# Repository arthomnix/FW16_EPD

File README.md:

# Framework Laptop 16 Touchscreen E-Paper Input Module

Touchscreen E-paper medium size input module for the Framework Laptop 16

_As featured on the [Framework 16 product page](https://frame.work/laptop16) and [Framework 2nd Gen Event](https://www.youtube.com/watch?v=-8k7jTF_JCg)_

**Firmware and software:** https://github.com/arthomnix/epd_firmware (also mirrored on [Tangled](https://tangled.sh/@arthomnix.dev/eepy))

## Legal

Copyright © 2024 arthomnix

This work is licensed under [Creative Commons Attribution-ShareAlike 4.0 International](https://creativecommons.org/licenses/by-sa/4.0).

Framework Laptop 16 Input Module footprints (`InputModule.pretty` folder) © 2023 Framework Computer, Inc. Licensed under [Creative Commons Attribution 4.0 International](https://creativecommons.org/licenses/by/4.0). Original available at https://github.com/FrameworkComputer/InputModules.

Hirose FH34SRJ footprints and symbols (`Hirose_FPC.pretty` folder; `FH34SRJ_*.kicad_sym`) © 2013-2024 SnapMagic. Licensed under [Creative Commons Attribution-ShareAlike 4.0 International](https://creativecommons.org/licenses/by-sa/4.0) with [Design Exception 1.0](https://www.snapeda.com/about/FAQ/#designexception). Originals available at https://www.snapeda.com/parts/FH34SRJ-6S-0.5SH%2850%29/Hirose%20Electric/view-part and https://www.snapeda.com/parts/FH34SRJ-24S-0.5SH%2850%29/Hirose%20Electric/view-part.

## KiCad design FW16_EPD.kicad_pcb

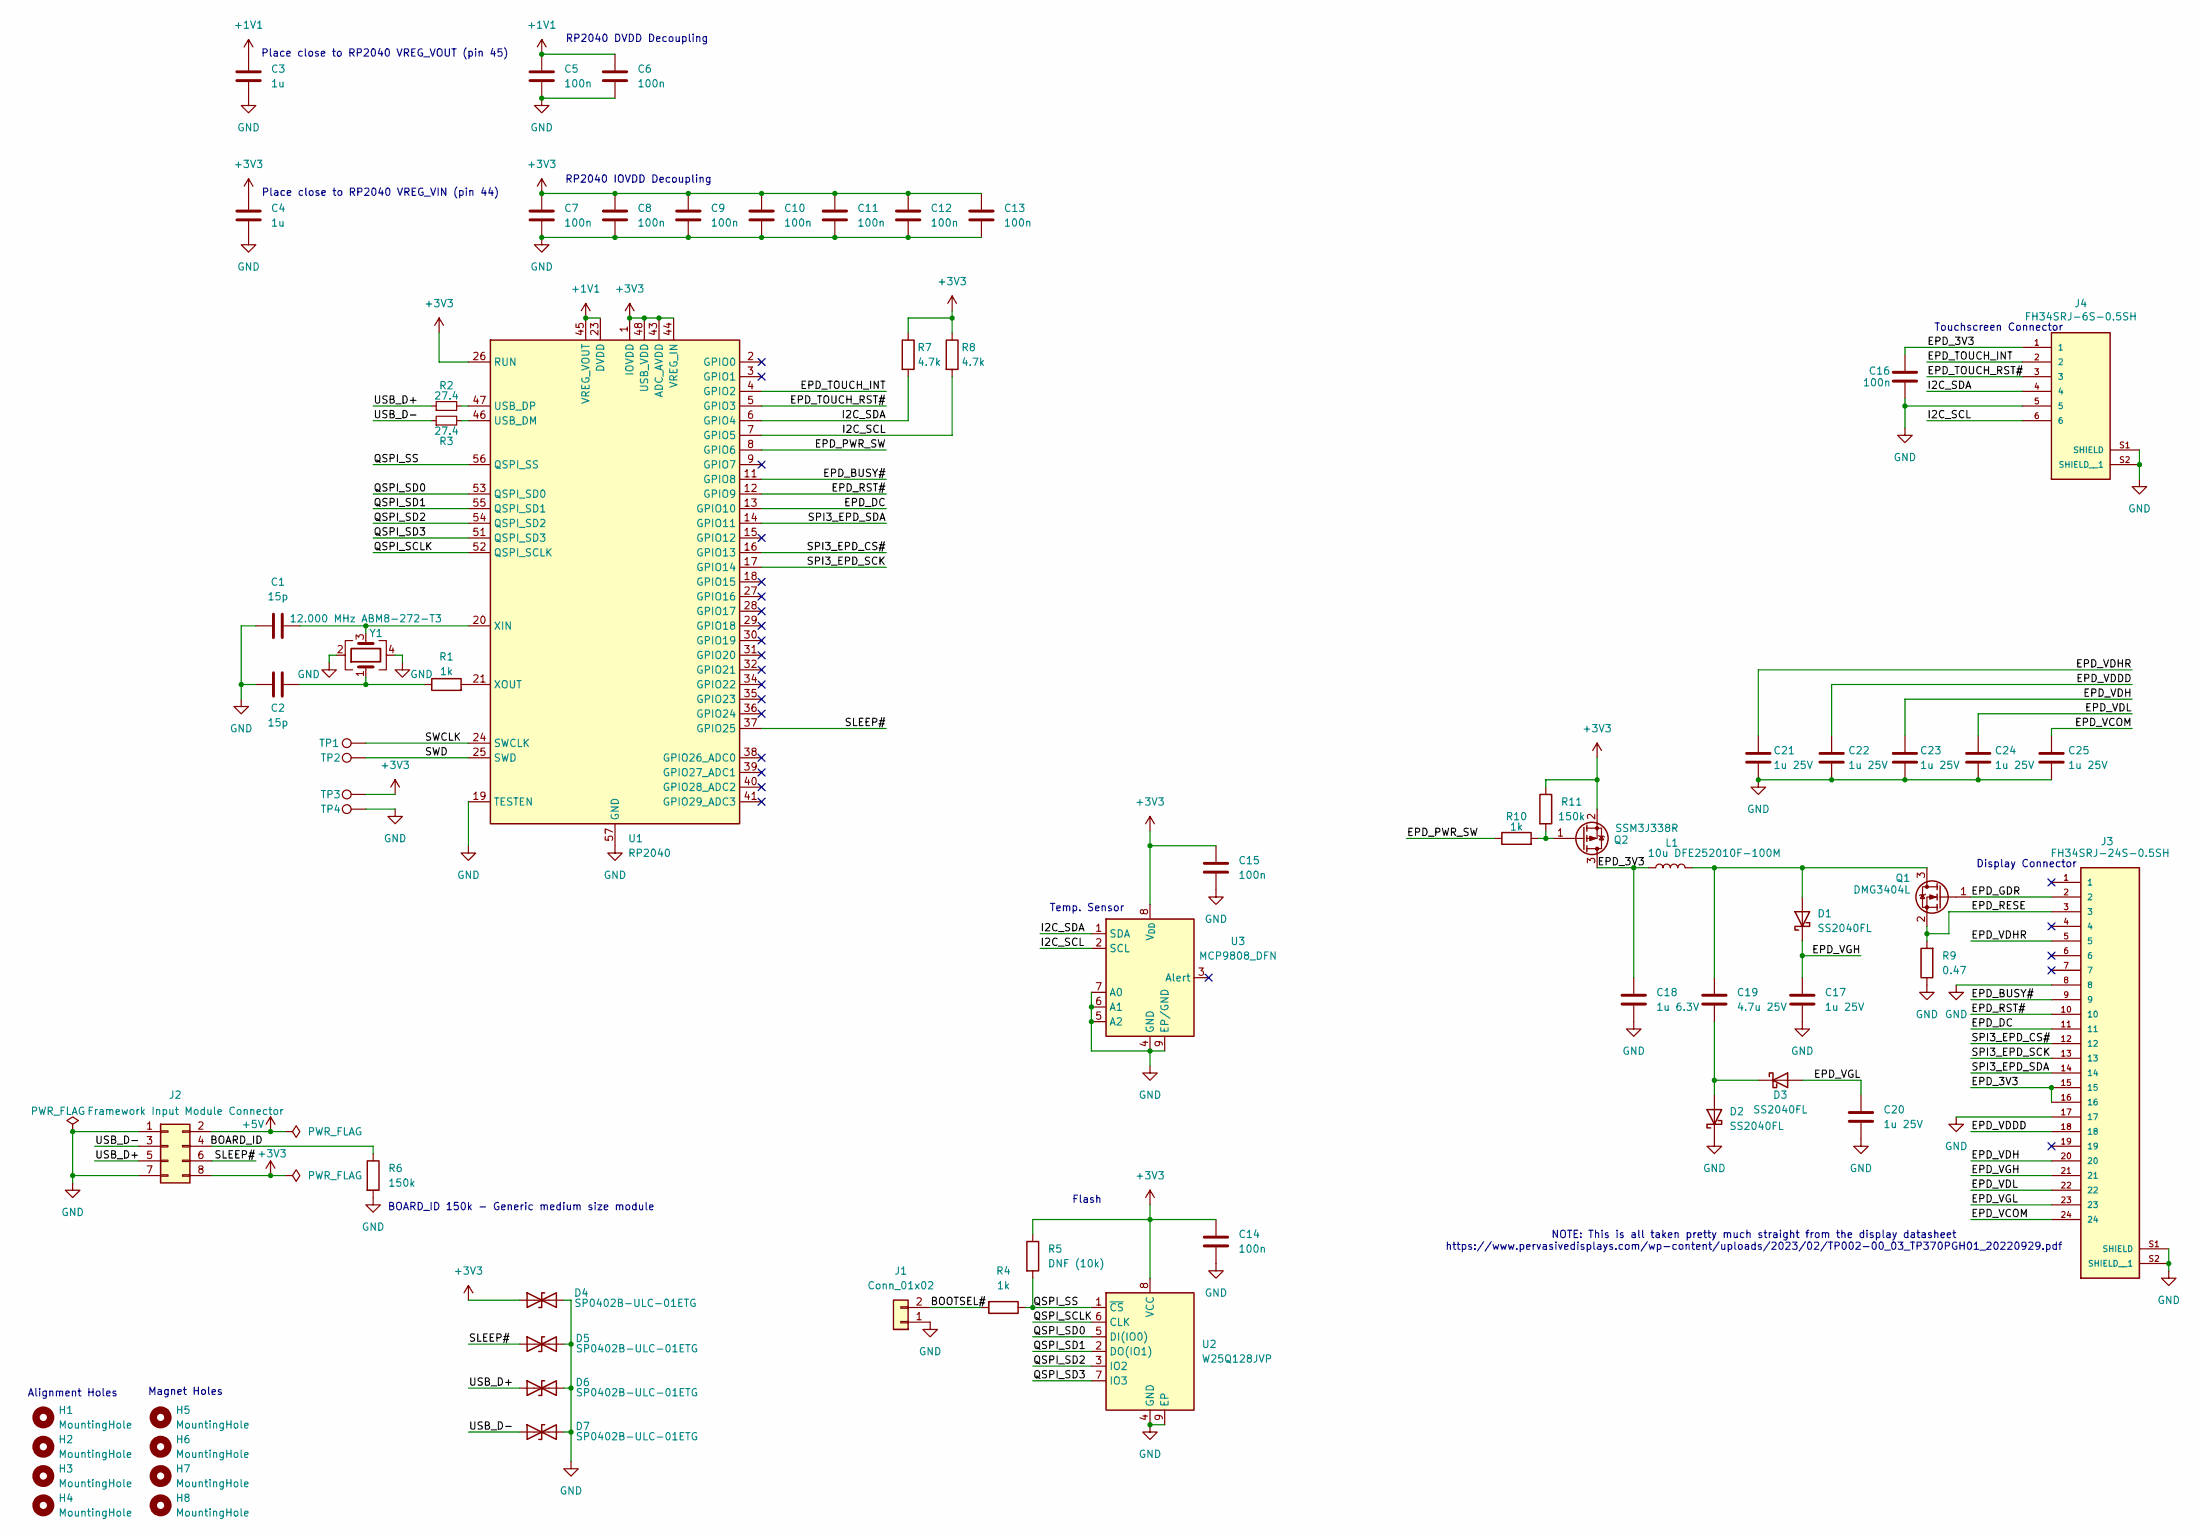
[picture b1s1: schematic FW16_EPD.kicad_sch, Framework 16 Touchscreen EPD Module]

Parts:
C1, C2: 15p; C_0402_1005Metric
C3, C4: 1u; C_0402_1005Metric
C5, C6, C7, C8, C9, C10, C11, C12, C13, C14, C15, C16: 100n; C_0402_1005Metric
C17, C20, C21, C22, C23, C24, C25: 1u 25V; C_0402_1005Metric
C18: 1u 6.3V; C_0402_1005Metric
C19: 4.7u 25V; C_0603_1608Metric
D1, D2, D3: SS2040FL; D_SOD-123F
D4, D5, D6, D7: SP0402B-ULC-01ETG; D_0402_1005Metric
H1, H2, H3, H4: MountingHole; MountingHole_2.1mm
H5, H6, H7, H8: MountingHole; MountingHole_3.7mm_Pad_24929
J1: Conn_01x02; SolderJumper-2_P1.3mm_Open_Pad1.0x1.5mm
J2: Framework Input Module Connector; PogoPads_2x4_P2.0mm
J3: FH34SRJ-24S-0.5SH; HRS_FH34SRJ-24S-0.5SH_50_
J4: FH34SRJ-6S-0.5SH; HRS_FH34SRJ-6S-0.5SH_50_
L1: 10u DFE252010F-100M; L_1008_2520Metric
Q1: DMG3404L; SOT-23
Q2: SSM3J338R; SOT-23
R1, R4, R10: 1k; R_0402_1005Metric
R2, R3: 27.4; R_0402_1005Metric
R5: DNF (10k); R_0402_1005Metric
R6, R11: 150k; R_0402_1005Metric
R7, R8: 4.7k; R_0402_1005Metric
R9: 0.47; R_0402_1005Metric
TP1, TP2, TP3, TP4: TestPoint; TestPoint_Pad_D2.5mm
U1: RP2040; QFN-56-1EP_7x7mm_P0.4mm_EP3.2x3.2mm
U2: W25Q128JVP; WSON-8-1EP_6x5mm_P1.27mm_EP3.4x4.3mm
U3: MCP9808_DFN; DFN-8-1EP_3x2mm_P0.5mm_EP1.7x1.4mm
Y1: 12.000 MHz ABM8-272-T3; Crystal_SMD_Abracon_ABM8G-4Pin_3.2x2.5mm

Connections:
+1V1: C3.1, C5.1, C6.1, U1.23 (DVDD), U1.45 (VREG_VOUT), U1.50 (DVDD)
+3V3: C4.1, C7.1, C8.1, C9.1, C10.1, C11.1, C12.1, C13.1, C14.1, C15.1, D4.1 (A1), J2.8, Q2.2 (S), R5.1, R7.1, R8.1, R11.1, TP3.1, U1.1 (IOVDD), U1.10 (IOVDD), U1.22 (IOVDD), U1.26 (RUN), U1.33 (IOVDD), U1.42 (IOVDD), U1.43 (ADC_AVDD), U1.44 (VREG_IN), U1.48 (USB_VDD), U1.49 (IOVDD), U2.8 (VCC), U3.8 (V_{DD})
+5V: J2.2
/BOARD_ID: J2.4, R6.1
/BOOTSEL#: J1.2, R4.2
/EPD_3V3: C16.2, C18.1, J3.15, J3.16, J4.1, L1.1, Q2.3 (D)
/EPD_BUSY#: J3.9, U1.11 (GPIO8)
/EPD_DC: J3.11, U1.13 (GPIO10)
/EPD_GDR: J3.2, Q1.1 (G)
/EPD_PWR_SW: R10.1, U1.8 (GPIO6)
/EPD_RESE: J3.3, Q1.2 (S), R9.2
/EPD_RST#: J3.10, U1.12 (GPIO9)
/EPD_TOUCH_INT: J4.2, U1.4 (GPIO2)
/EPD_TOUCH_RST#: J4.3, U1.5 (GPIO3)
/EPD_VCOM: C25.1, J3.24
/EPD_VDDD: C22.1, J3.18
/EPD_VDH: C23.1, J3.20
/EPD_VDHR: C21.1, J3.5
/EPD_VDL: C24.1, J3.22
/EPD_VGH: C17.1, D1.1 (K), J3.21
/EPD_VGL: C20.1, D3.2 (A), J3.23
/I2C_SCL: J4.6, R8.2, U1.7 (GPIO5), U3.2 (SCL)
/I2C_SDA: J4.4, R7.2, U1.6 (GPIO4), U3.1 (SDA)
/QSPI_SCLK: U1.52 (QSPI_SCLK), U2.6 (CLK)
/QSPI_SD0: U1.53 (QSPI_SD0), U2.5 (DI(IO0))
/QSPI_SD1: U1.55 (QSPI_SD1), U2.2 (DO(IO1))
/QSPI_SD2: U1.54 (QSPI_SD2), U2.3 (IO2)
/QSPI_SD3: U1.51 (QSPI_SD3), U2.7 (IO3)
/QSPI_SS: R4.1, R5.2, U1.56 (QSPI_SS), U2.1 (~CS)
/SLEEP#: D5.1 (A1), J2.6, U1.37 (GPIO25)
/SPI3_EPD_CS#: J3.12, U1.16 (GPIO13)
/SPI3_EPD_SCK: J3.13, U1.17 (GPIO14)
/SPI3_EPD_SDA: J3.14, U1.14 (GPIO11)
/SWCLK: TP1.1, U1.24 (SWCLK)
/SWD: TP2.1, U1.25 (SWD)
/USB_D+: D6.1 (A1), J2.5, R2.1
/USB_D-: D7.1 (A1), J2.3, R3.1
GND: C1.1, C2.1, C3.2, C4.2, C5.2, C6.2, C7.2, C8.2, C9.2, C10.2, C11.2, C12.2, C13.2, C14.2, C15.2, C16.1, C17.2, C18.2, C20.2, C21.2, C22.2, C23.2, C24.2, C25.2, D2.1 (K), D4.2 (A2), D5.2 (A2), D6.2 (A2), D7.2 (A2), J1.1, J2.1, J2.7, J3.8, J3.17, J3.S1 (SHIELD), J3.S2 (SHIELD__1), J4.5, J4.S1 (SHIELD), J4.S2 (SHIELD__1), R6.2, R9.1, TP4.1, U1.19 (TESTEN), U1.57 (GND), U2.4 (GND), U2.9 (EP), U3.4 (GND), U3.5 (A2), U3.6 (A1), U3.7 (A0), U3.9 (EP/GND), Y1.2, Y1.4
unnamed: C2.2, R1.1, Y1.1
unnamed: C19.1, D1.2 (A), L1.2, Q1.3 (D)
unnamed: C19.2, D2.2 (A), D3.1 (K)
unnamed: Q2.1 (G), R10.2, R11.2
unnamed: R3.2, U1.46 (USB_DM)
unnamed: R2.2, U1.47 (USB_DP)
unnamed: C1.2, U1.20 (XIN), Y1.3
unnamed: R1.2, U1.21 (XOUT)

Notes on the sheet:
NOTE: This is all taken pretty much straight from the display datasheet https://www.pervasivedisplays.com/wp-content/uploads/2023/02/TP002-00_03_TP370PGH01_20220929.pdf
Magnet Holes
Place close to RP2040 VREG_VOUT (pin 45)
RP2040 DVDD Decoupling
Flash
Touchscreen Connector
RP2040 IOVDD Decoupling
Display Connector
BOARD_ID 150k - Generic medium size module
Place close to RP2040 VREG_VIN (pin 44)
Alignment Holes
Temp. Sensor

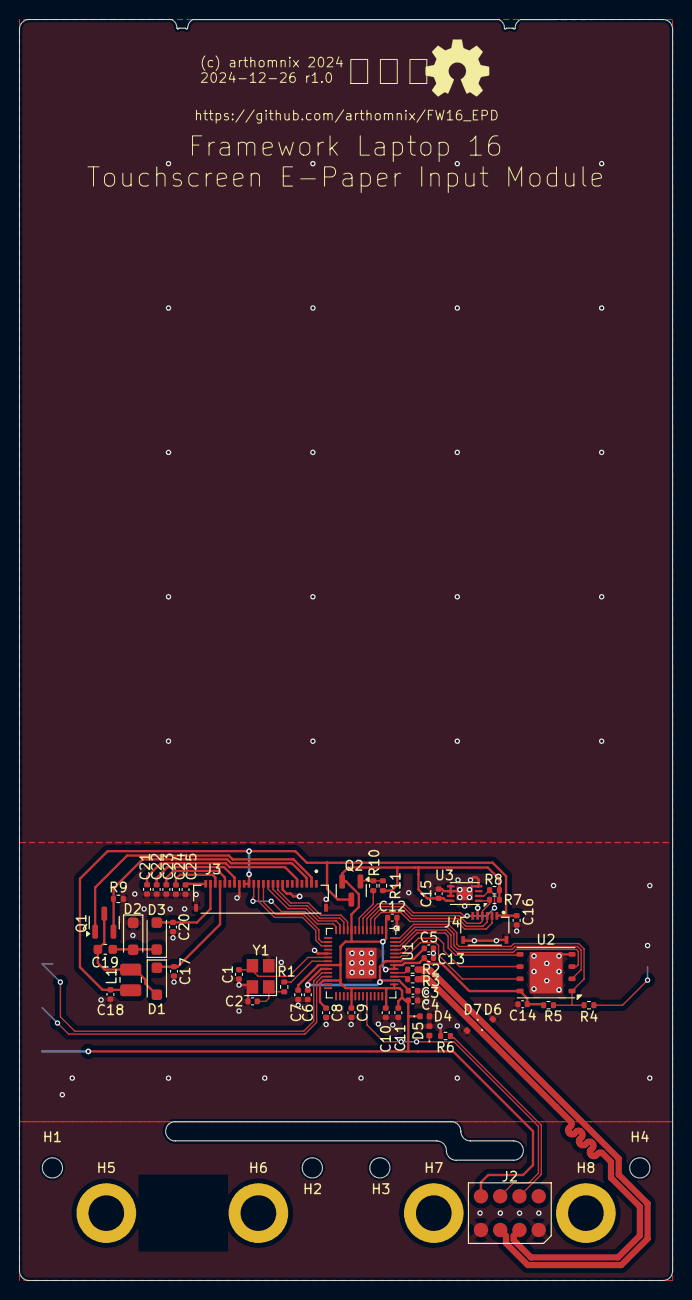
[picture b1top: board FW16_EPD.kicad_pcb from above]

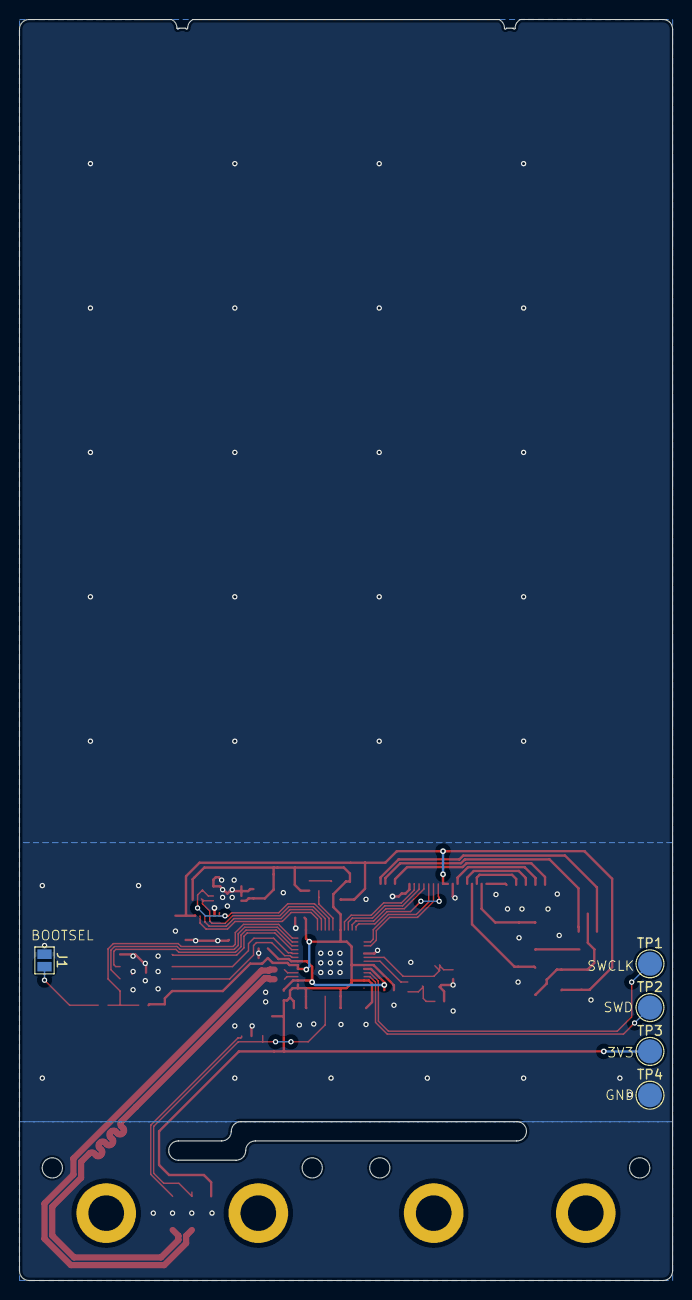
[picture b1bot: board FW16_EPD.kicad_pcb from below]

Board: 2 copper layers, 67.8 x 131.0 mm, 66 parts (5 on the bottom side), 45 nets.

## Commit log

2024-07-09 pcb: add CC and OSHW symbols; silkscreen rearrangements
2024-07-10 sch/pcb: add TVS diodes; thicker traces for EPD DC/DC
2024-07-10 pcb: update dates
2024-07-10 pcb: measurements corrections
2024-07-11 pcb: clean up epd gnd connection
2024-07-11 pcb: set solder mask expansion for JLC
2024-07-11 pcb: more closely match reference board outline
2024-10-03 finishing touches
2024-11-28 move spi3 traces away from crystal
2024-11-29 update date
2024-12-03 move crystal for better clearance with FFC
2024-12-05 add 3d models for fpc
2024-12-26 remove paste layer from hole footprint
2025-01-07 Add image to readme
